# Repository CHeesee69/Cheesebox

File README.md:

# Cheesebox
The cheesebox is a small emulation device that uses a CM5 board. It will have the power to emulate 5th-gen and select 6th- and 7th-gen hardware. I plan for it to be kind of flat so I can make a screen, battery, and controller add-on down the line to make it portable. Why is it called "The Cheesebox"? Because I like cheese. Duh.

# Features

Cool Design

Power Light

Two USB-C Ports

Two USB-A 3.0 Ports

Two USB-A 2.0 Ports

Magjack Ethernet Port

3.5 mm Headphone Jack

Micro SD Card Slot

2242 M.2 SSD or NVMe Slot (3rd Gen)

HDMI Output

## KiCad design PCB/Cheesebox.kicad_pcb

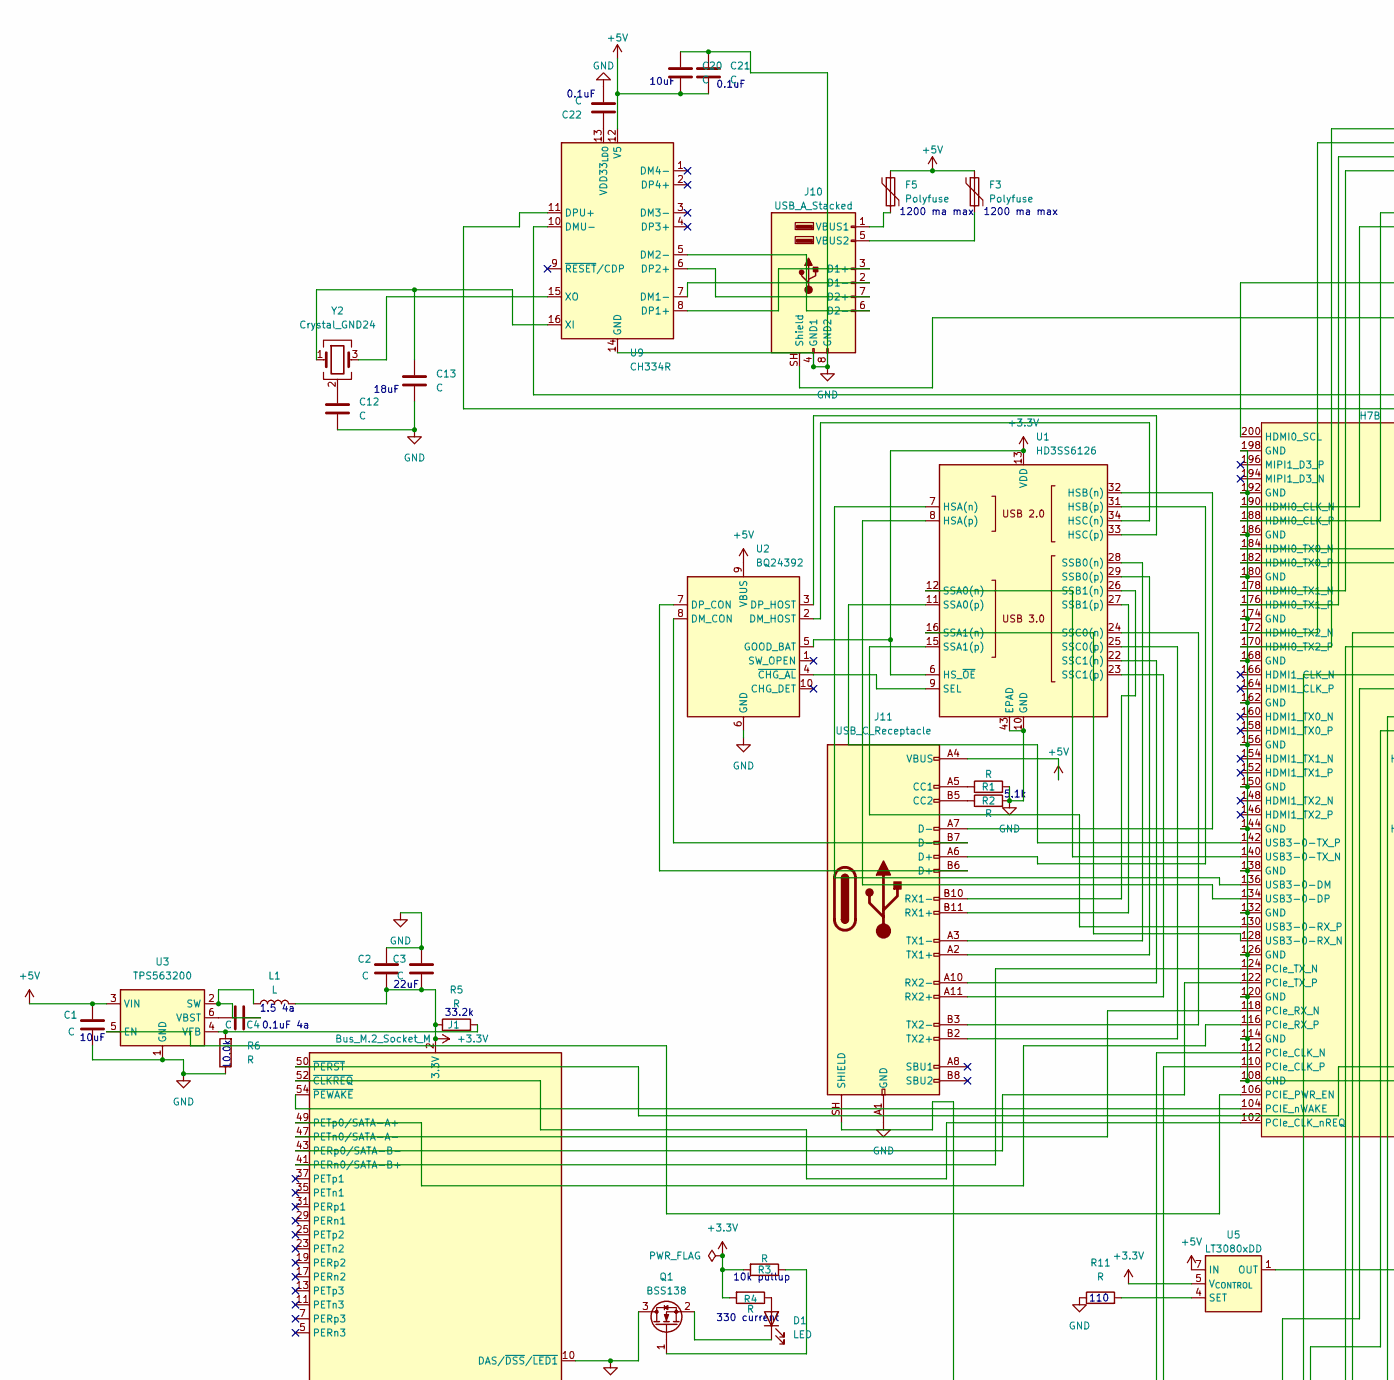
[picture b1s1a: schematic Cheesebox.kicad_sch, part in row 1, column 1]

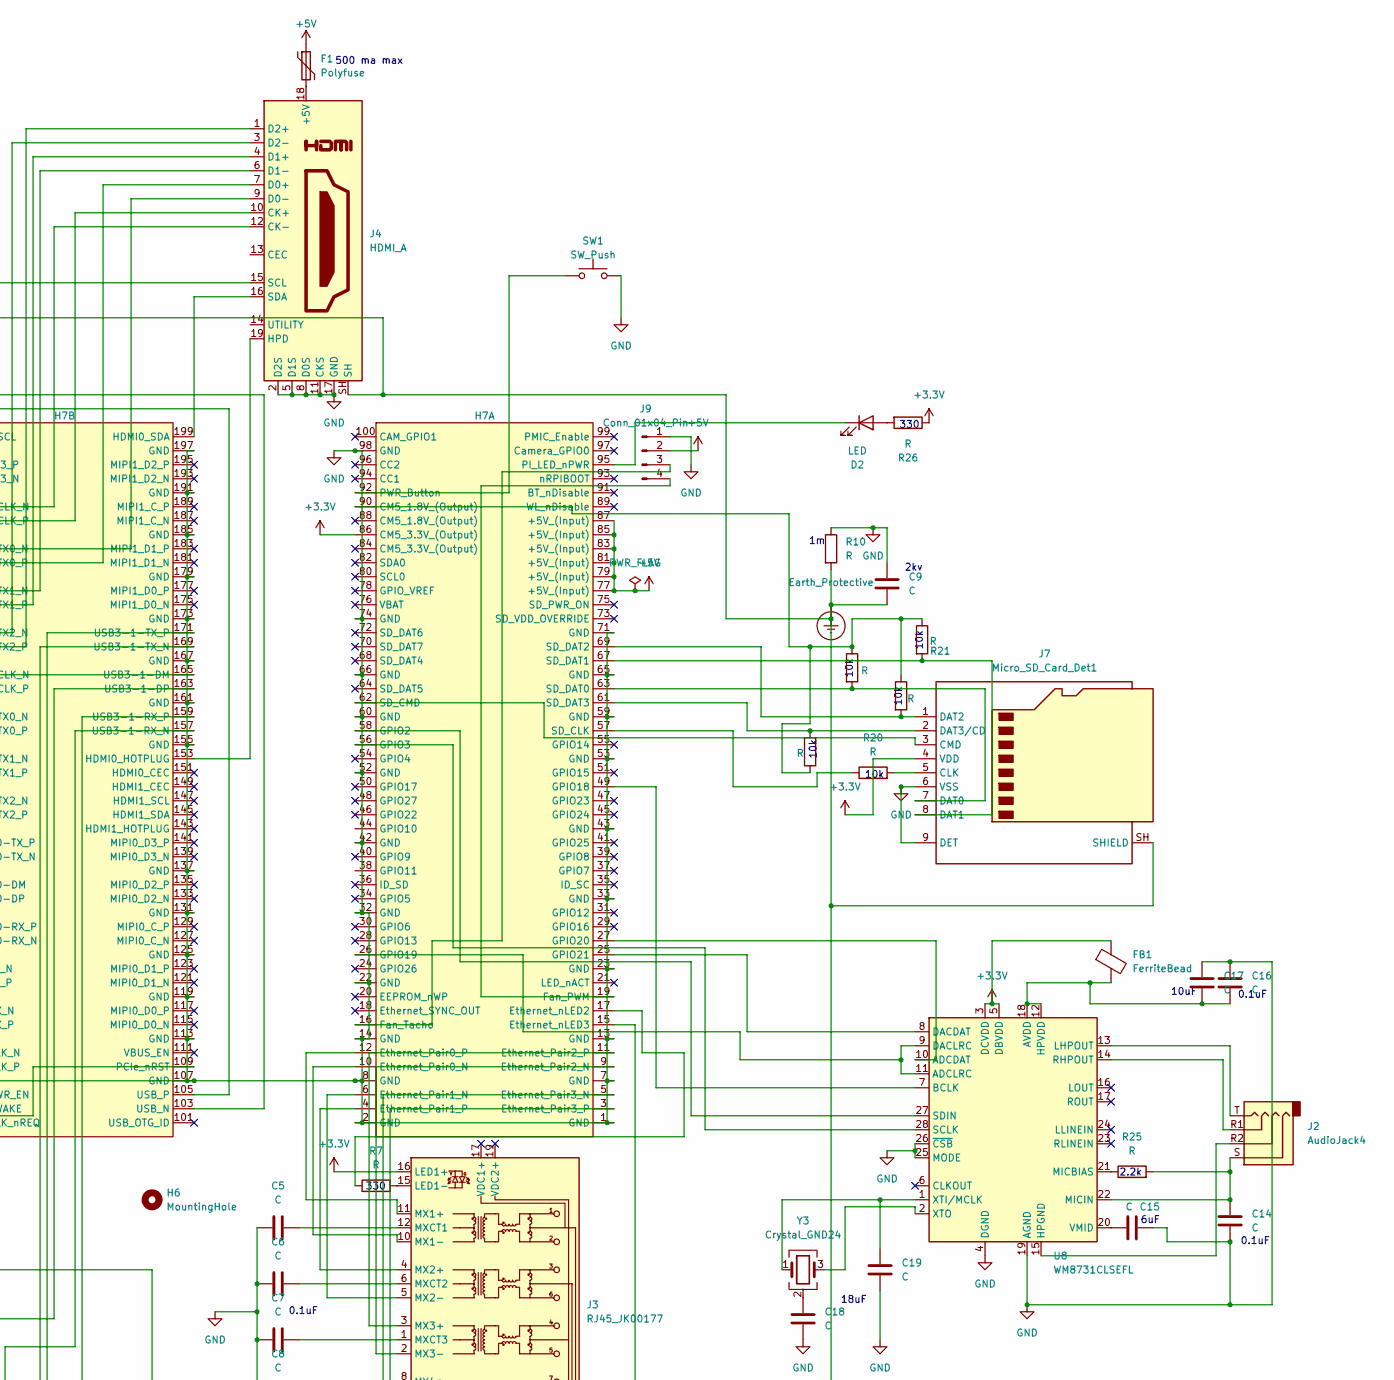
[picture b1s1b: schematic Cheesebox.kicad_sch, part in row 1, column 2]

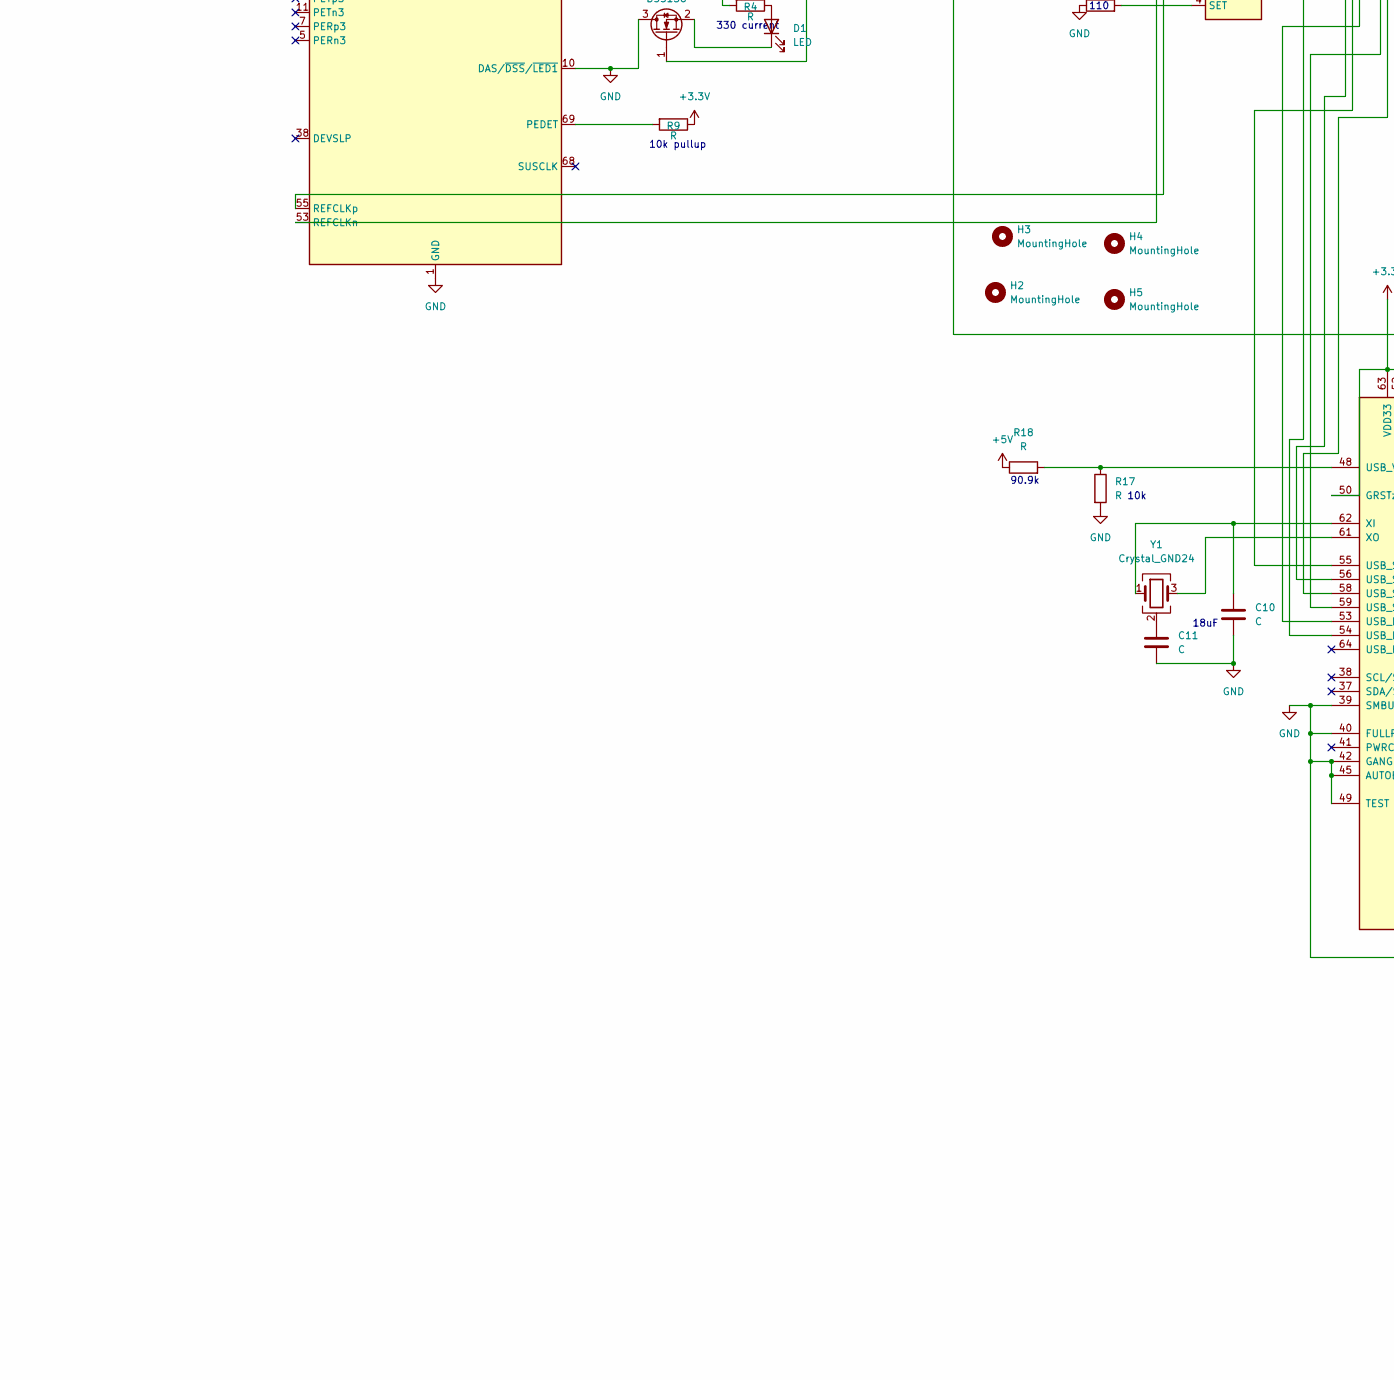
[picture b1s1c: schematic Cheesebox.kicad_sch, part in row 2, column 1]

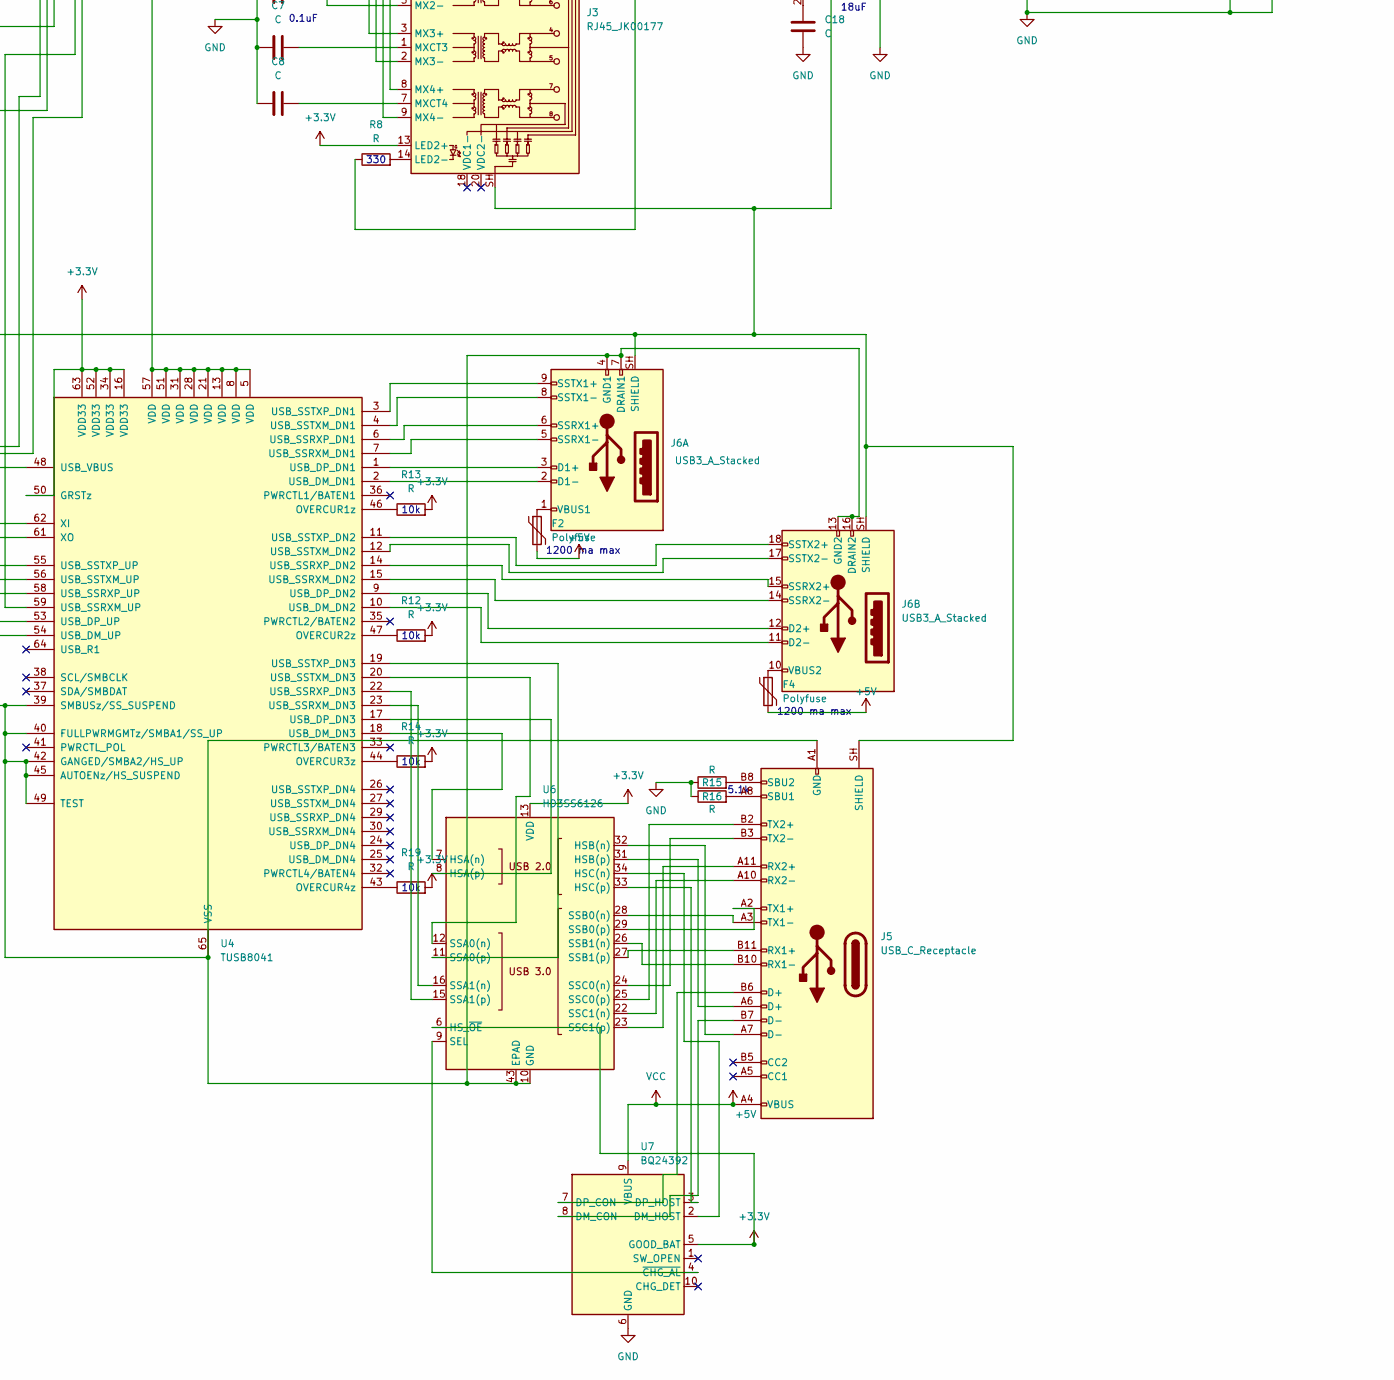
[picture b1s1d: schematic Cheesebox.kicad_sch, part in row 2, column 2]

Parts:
C1, C2, C3, C10, C11, C12, C13, C15, C17, C18, C19, C20: C; C_0805_2012Metric_Pad1.18x1.45mm_HandSolder
C4, C5, C6, C7, C8, C9, C14, C16, C21, C22: C; C_0603_1608Metric_Pad1.08x0.95mm_HandSolder
D1, D2: LED; LED_0603_1608Metric_Pad1.05x0.95mm_HandSolder
F1: Polyfuse; Fuse_1206_3216Metric_Pad1.42x1.75mm_HandSolder
F2, F3, F4, F5: Polyfuse; Fuse_1210_3225Metric_Pad1.42x2.65mm_HandSolder
FB1: FerriteBead; L_0805_2012Metric_Pad1.05x1.20mm_HandSolder
H2, H3, H4, H5: MountingHole; MountingHole_2.5mm
H6: MountingHole; MountingHole_2.2mm_M2
H7: RaspberryPi-CM5-Carrier-Short-NPTH-Silk
J1: Bus_M.2_Socket_M; CONN67_2199230_TEC
J2: AudioJack4; Jack_3.5mm_CUI_SJ-3524-SMT_Horizontal
J3: RJ45_JK00177; RJ45_Pulse_JK00177NL_Horizontal
J4: HDMI_A; HDMI_A_Amphenol_10029449-x01xLF_Horizontal
J5, J11: USB_C_Receptacle; USB_C_Receptacle_Amphenol_12401548E4-2A_CircularHoles
J6: USB3_A_Stacked; USB3_A_Molex_48406-0001_Horizontal_Stacked
J7: Micro_SD_Card_Det1; microSD_HC_Hirose_DM3AT-SF-PEJM5
J9: Conn_01x04_Pin; FanPinHeader_1x04_P2.54mm_Vertical
J10: USB_A_Stacked; USB_A_Wuerth_61400826021_Horizontal_Stacked
L1: L; L_Coilcraft_XAL4040-XXX
Q1: BSS138; SOT-23
R1, R2, R3, R4, R7, R8, R9, R10, R11, R12, R13, R14, R15, R16, R19, R20, R21, R22, R23, R24, R25, R26: R; R_0805_2012Metric_Pad1.20x1.40mm_HandSolder
R5, R6, R17, R18: R; R_1206_3216Metric_Pad1.30x1.75mm_HandSolder
SW1: SW_Push; SW_PUSH_6mm_H5mm
U1, U6: HD3SS6126; WQFN-42-1EP_3.5x9mm_P0.5mm_EP2.05x7.55mm_ThermalVias
U2, U7: BQ24392; Texas_R-PUQFN-N10
U3: TPS563200; SOT-23-6
U4: TUSB8041; QFN-64-1EP_9x9mm_P0.5mm_EP6x6mm_ThermalVias
U5: LT3080xDD; DFN-8-1EP_3x3mm_P0.5mm_EP1.66x2.38mm
U8: WM8731CLSEFL; QFN-28-1EP_5x5mm_P0.5mm_EP3.35x3.35mm
U9: CH334R; QSOP-16_3.9x4.9mm_P0.635mm
Y1, Y2, Y3: Crystal_GND24; Resonator-3Pin_W6.0mm_H3.0mm

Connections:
+3.3V: C2.2, C3.2, FB1.1, H7.86 (CM5_3.3V_(Output)), J1.2 (3.3V), J1.4 (3.3V), J1.12 (3.3V), J1.14 (3.3V), J1.16 (3.3V), J1.18 (3.3V), J1.70 (3.3V), J1.72 (3.3V), J1.74 (3.3V), J3.13 (LED2+), J3.16 (LED1+), J7.4 (VDD), L1.2, R3.2, R4.2, R5.1, R9.1, R12.2, R13.2, R14.2, R19.2, R26.1, U1.6 (HS_~OE), U1.13 (VDD), U1.20 (VDD), U1.30 (VDD), U2.5 (GOOD_BAT), U4.16 (VDD33), U4.34 (VDD33), U4.50 (GRSTz), U4.52 (VDD33), U4.63 (VDD33), U5.5 (V_{CONTROL}), U6.6 (HS_~OE), U6.13 (VDD), U6.20 (VDD), U6.30 (VDD), U7.5 (GOOD_BAT), U8.3 (DCVDD), U8.5 (DBVDD)
+5V: C1.1, C20.1, C21.2, F1.1, F2.2, F3.1, F4.2, F5.1, H7.77 (+5V_(Input)), H7.79 (+5V_(Input)), H7.81 (+5V_(Input)), H7.83 (+5V_(Input)), H7.85 (+5V_(Input)), H7.87 (+5V_(Input)), J5.A4 (VBUS), J5.A9 (VBUS), J5.B4 (VBUS), J5.B9 (VBUS), J9.2, J11.A4 (VBUS), J11.A9 (VBUS), J11.B4 (VBUS), J11.B9 (VBUS), R18.1, U2.9 (VBUS), U3.3 (VIN), U5.7 (IN), U5.8 (IN), U7.9 (VBUS), U9.12 (V5)
Earth_Protective: C9.2, J3.SH, J4.SH, J5.SH (SHIELD), J6.SH (SHIELD), J7.SH (SHIELD), J10.SH (Shield), J11.SH (SHIELD), R10.2
GND: C1.2, C2.1, C3.1, C5.1, C6.1, C7.1, C8.1, C9.1, C10.1, C11.1, C12.1, C13.1, C14.2, C15.1, C16.1, C17.2, C18.1, C19.1, C20.2, C21.1, C22.2, H7.1 (GND), H7.2 (GND), H7.7 (GND), H7.8 (GND), H7.13 (GND), H7.14 (GND), H7.22 (GND), H7.23 (GND), H7.32 (GND), H7.33 (GND), H7.42 (GND), H7.43 (GND), H7.52 (GND), H7.53 (GND), H7.59 (GND), H7.60 (GND), H7.65 (GND), H7.66 (GND), H7.71 (GND), H7.74 (GND), H7.98 (GND), H7.107 (GND), H7.108 (GND), H7.113 (GND), H7.114 (GND), H7.119 (GND), H7.120 (GND), H7.125 (GND), H7.126 (GND), H7.131 (GND), H7.132 (GND), H7.137 (GND), H7.138 (GND), H7.144 (GND), H7.150 (GND), H7.155 (GND), H7.156 (GND), H7.161 (GND), H7.162 (GND), H7.167 (GND), H7.168 (GND), H7.173 (GND), H7.174 (GND), H7.179 (GND), H7.180 (GND), H7.185 (GND), H7.186 (GND), H7.191 (GND), H7.192 (GND), H7.197 (GND), H7.198 (GND), J1.1 (GND), J1.3 (GND), J1.9 (GND), J1.10 (DAS/~DSS/~LED1), J1.15 (GND), J1.21 (GND), J1.27 (GND), J1.33 (GND), J1.39 (GND), J1.45 (GND), J1.51 (GND), J1.57 (GND), J1.71 (GND), J1.73 (GND), J1.75 (GND), J4.2 (D2S), J4.5 (D1S), J4.8 (D0S), J4.11 (CKS), J4.17 (GND), J5.A1 (GND), J5.A12 (GND), J5.B1 (GND), J5.B12 (GND), J6.4 (GND1), J6.7 (DRAIN1), J6.13 (GND2), J6.16 (DRAIN2), J7.6 (VSS), J7.9 (DET), J9.1, J10.4 (GND1), J10.8 (GND2), J11.A1 (GND), J11.A12 (GND), J11.B1 (GND), J11.B12 (GND), Q1.3 (D), R1.2, R2.2, R6.1, R10.1, R11.1, R15.1, R16.1, R17.2, SW1.2, U1.10 (GND), U1.14 (GND), U1.17 (GND), U1.19 (GND), U1.21 (GND), U1.43 (EPAD), U2.6 (GND), U3.1 (GND), U4.39 (SMBUSz/SS_SUSPEND), U4.40 (FULLPWRMGMTz/SMBA1/SS_UP), U4.42 (GANGED/SMBA2/HS_UP), U4.45 (AUTOENz/HS_SUSPEND), U4.49 (TEST), U4.65 (VSS), U6.10 (GND), U6.14 (GND), U6.17 (GND), U6.19 (GND), U6.21 (GND), U6.43 (EPAD), U7.6 (GND), U8.4 (DGND), U8.19 (AGND), U8.25 (MODE), U8.26 (~CSB), U8.29 (AGND), U9.14 (GND)
unnamed: C11.2, Y1.2 (G), Y1.4 (G)
unnamed: C12.2, Y2.2 (G), Y2.4 (G)
unnamed: C18.2, Y3.2 (G), Y3.4 (G)
unnamed: D1.2 (A), R4.1
unnamed: D1.1 (K), Q1.2 (S)
unnamed: D2.2 (A), R26.2
unnamed: D2.1 (K), H7.95 (PI_LED_nPWR)
unnamed: H7.90 (CM5_1.8V_(Output)), R21.1, R22.1, R23.1, R24.1
unnamed: H7.10 (Ethernet_Pair0_N), J3.10 (MX1-)
unnamed: H7.12 (Ethernet_Pair0_P), J3.11 (MX1+)
unnamed: H7.6 (Ethernet_Pair1_N), J3.5 (MX2-)
unnamed: H7.4 (Ethernet_Pair1_P), J3.4 (MX2+)
unnamed: H7.9 (Ethernet_Pair2_N), J3.2 (MX3-)
unnamed: H7.11 (Ethernet_Pair2_P), J3.3 (MX3+)
unnamed: H7.5 (Ethernet_Pair3_N), J3.9 (MX4-)
unnamed: H7.3 (Ethernet_Pair3_P), J3.8 (MX4+)
unnamed: H7.17 (Ethernet_nLED2), R7.1
unnamed: H7.15 (Ethernet_nLED3), R8.1
unnamed: H7.19 (Fan_PWM), J9.4
unnamed: H7.16 (Fan_Tacho), J9.3
unnamed: H7.58 (GPIO2), U8.27 (SDIN)
unnamed: H7.56 (GPIO3), U8.28 (SCLK)
unnamed: H7.49 (GPIO18), U8.7 (BCLK)
unnamed: H7.26 (GPIO19), U8.9 (DACLRC), U8.11 (ADCLRC)
unnamed: H7.27 (GPIO20), U8.10 (ADCDAT)
unnamed: H7.25 (GPIO21), U8.8 (DACDAT)
unnamed: H7.92 (PWR_Button), SW1.1
unnamed: H7.57 (SD_CLK), R20.1
unnamed: H7.62 (SD_CMD), J7.3 (CMD)
unnamed: H7.63 (SD_DAT0), J7.7 (DAT0), R22.2
unnamed: H7.67 (SD_DAT1), J7.8 (DAT1), R21.2
unnamed: H7.69 (SD_DAT2), J7.1 (DAT2), R23.2
unnamed: H7.61 (SD_DAT3), J7.2 (DAT3/CD), R24.2
unnamed: H7.190 (HDMI0_CLK_N), J4.12 (CK-)
unnamed: H7.188 (HDMI0_CLK_P), J4.10 (CK+)
unnamed: H7.153 (HDMI0_HOTPLUG), J4.19 (HPD)
unnamed: H7.200 (HDMI0_SCL), J4.15 (SCL)
unnamed: H7.199 (HDMI0_SDA), J4.16 (SDA)
unnamed: H7.184 (HDMI0_TX0_N), J4.9 (D0-)
unnamed: H7.182 (HDMI0_TX0_P), J4.7 (D0+)
unnamed: H7.178 (HDMI0_TX1_N), J4.6 (D1-)
unnamed: H7.176 (HDMI0_TX1_P), J4.4 (D1+)
unnamed: H7.172 (HDMI0_TX2_N), J4.3 (D2-)
unnamed: H7.170 (HDMI0_TX2_P), J4.1 (D2+)
unnamed: H7.106 (PCIE_PWR_EN), U3.5 (EN)
unnamed: H7.104 (PCIE_nWAKE), J1.54 (~PEWAKE)
unnamed: H7.112 (PCIe_CLK_N), J1.53 (REFCLKn)
unnamed: H7.110 (PCIe_CLK_P), J1.55 (REFCLKp)
unnamed: H7.102 (PCIe_CLK_nREQ), J1.52 (~CLKREQ)
unnamed: H7.118 (PCIe_RX_N), J1.47 (PETn0/SATA-A-)
unnamed: H7.116 (PCIe_RX_P), J1.49 (PETp0/SATA-A+)
unnamed: H7.124 (PCIe_TX_N), J1.41 (PERn0/SATA-B+)
unnamed: H7.122 (PCIe_TX_P), J1.43 (PERp0/SATA-B-)
unnamed: H7.109 (PCIe_nRST), J1.50 (~PERST)
unnamed: H7.136 (USB3-0-DM), U1.7 (HSA(n))
unnamed: H7.134 (USB3-0-DP), U1.8 (HSA(p))
unnamed: H7.128 (USB3-0-RX_N), U1.16 (SSA1(n))
unnamed: H7.130 (USB3-0-RX_P), U1.15 (SSA1(p))
unnamed: H7.140 (USB3-0-TX_N), U1.12 (SSA0(n))
unnamed: H7.142 (USB3-0-TX_P), U1.11 (SSA0(p))
unnamed: H7.165 (USB3-1-DM), U4.54 (USB_DM_UP)
unnamed: H7.163 (USB3-1-DP), U4.53 (USB_DP_UP)
unnamed: H7.157 (USB3-1-RX_N), U4.59 (USB_SSRXM_UP)
unnamed: H7.159 (USB3-1-RX_P), U4.58 (USB_SSRXP_UP)
unnamed: H7.169 (USB3-1-TX_N), U4.56 (USB_SSTXM_UP)
unnamed: H7.171 (USB3-1-TX_P), U4.55 (USB_SSTXP_UP)
unnamed: H7.103 (USB_N), U9.10 (DMU-)
unnamed: H7.105 (USB_P), U9.11 (DPU+)
unnamed: J1.69 (PEDET), R9.2
unnamed: J3.15 (LED1-), R7.2
unnamed: J3.14 (LED2-), R8.2
unnamed: C5.2, J3.12 (MXCT1)
unnamed: C6.2, J3.6 (MXCT2)
unnamed: C7.2, J3.1 (MXCT3)
unnamed: C8.2, J3.7 (MXCT4)
unnamed: F1.2, J4.18 (+5V)
unnamed: J5.B11 (RX1+), U6.27 (SSB1(p))
unnamed: J5.B10 (RX1-), U6.26 (SSB1(n))
unnamed: J5.A11 (RX2+), U6.23 (SSC1(p))
unnamed: J5.A10 (RX2-), U6.22 (SSC1(n))
unnamed: J5.A8 (SBU1), R16.2
unnamed: J5.B8 (SBU2), R15.2
unnamed: J5.A2 (TX1+), U6.29 (SSB0(p))
unnamed: J5.A3 (TX1-), U6.28 (SSB0(n))
unnamed: J5.B2 (TX2+), U6.25 (SSC0(p))
unnamed: J5.B3 (TX2-), U6.24 (SSC0(n))
unnamed: J6.3 (D1+), U4.1 (USB_DP_DN1)
unnamed: J6.2 (D1-), U4.2 (USB_DM_DN1)
unnamed: J6.6 (SSRX1+), U4.6 (USB_SSRXP_DN1)
unnamed: J6.5 (SSRX1-), U4.7 (USB_SSRXM_DN1)
unnamed: J6.9 (SSTX1+), U4.3 (USB_SSTXP_DN1)
unnamed: J6.8 (SSTX1-), U4.4 (USB_SSTXM_DN1)
unnamed: F2.1, J6.1 (VBUS1)
unnamed: J6.12 (D2+), U4.9 (USB_DP_DN2)
unnamed: J6.11 (D2-), U4.10 (USB_DM_DN2)
unnamed: J6.15 (SSRX2+), U4.14 (USB_SSRXP_DN2)
unnamed: J6.14 (SSRX2-), U4.15 (USB_SSRXM_DN2)
unnamed: J6.18 (SSTX2+), U4.11 (USB_SSTXP_DN2)
unnamed: J6.17 (SSTX2-), U4.12 (USB_SSTXM_DN2)
unnamed: F4.1, J6.10 (VBUS2)
unnamed: J7.5 (CLK), R20.2
unnamed: J10.3 (D1+), U9.8 (DP1+)
unnamed: J10.2 (D1-), U9.7 (DM1-)
unnamed: J10.7 (D2+), U9.6 (DP2+)
unnamed: J10.6 (D2-), U9.5 (DM2-)
unnamed: F5.2, J10.1 (VBUS1)
unnamed: F3.2, J10.5 (VBUS2)
unnamed: J11.A5 (CC1), R1.1
unnamed: J11.B5 (CC2), R2.1
unnamed: J11.B11 (RX1+), U1.27 (SSB1(p))
unnamed: J11.B10 (RX1-), U1.26 (SSB1(n))
unnamed: J11.A11 (RX2+), U1.23 (SSC1(p))
unnamed: J11.A10 (RX2-), U1.22 (SSC1(n))
unnamed: J11.A2 (TX1+), U1.29 (SSB0(p))
unnamed: J11.A3 (TX1-), U1.28 (SSB0(n))
unnamed: J11.B2 (TX2+), U1.25 (SSC0(p))
unnamed: J11.B3 (TX2-), U1.24 (SSC0(n))
unnamed: Q1.1 (G), R3.1
unnamed: J11.A7 (D-), U1.32 (HSB(n))
unnamed: J11.A6 (D+), U1.31 (HSB(p))
unnamed: U1.34 (HSC(n)), U2.2 (DM_HOST)
unnamed: U1.33 (HSC(p)), U2.3 (DP_HOST)
unnamed: U1.9 (SEL), U2.4 (~CHG_AL)
unnamed: J11.B7 (D-), U2.8 (DM_CON)
unnamed: J11.B6 (D+), U2.7 (DP_CON)
unnamed: C4.2, L1.1, U3.2 (SW)
unnamed: C4.1, U3.6 (VBST)
unnamed: R5.2, R6.2, U3.4 (VFB)
unnamed: R13.1, U4.46 (OVERCUR1z)
unnamed: R12.1, U4.47 (OVERCUR2z)
unnamed: R14.1, U4.44 (OVERCUR3z)
unnamed: R19.1, U4.43 (OVERCUR4z)
unnamed: U4.18 (USB_DM_DN3), U6.7 (HSA(n))
unnamed: U4.17 (USB_DP_DN3), U6.8 (HSA(p))
unnamed: U4.23 (USB_SSRXM_DN3), U6.16 (SSA1(n))
unnamed: U4.22 (USB_SSRXP_DN3), U6.15 (SSA1(p))
unnamed: U4.20 (USB_SSTXM_DN3), U6.12 (SSA0(n))
unnamed: U4.19 (USB_SSTXP_DN3), U6.11 (SSA0(p))
unnamed: R17.1, R18.2, U4.48 (USB_VBUS)
unnamed: U4.5 (VDD), U4.8 (VDD), U4.13 (VDD), U4.21 (VDD), U4.28 (VDD), U4.31 (VDD), U4.51 (VDD), U4.57 (VDD), U5.1 (OUT), U5.2 (OUT), U5.3 (OUT), U5.9 (OUT)
unnamed: C10.2, U4.62 (XI), Y1.1
unnamed: U4.61 (XO), Y1.3
unnamed: R11.2, U5.4 (SET)
unnamed: J5.A7 (D-), U6.32 (HSB(n))
unnamed: J5.A6 (D+), U6.31 (HSB(p))
unnamed: U6.34 (HSC(n)), U7.2 (DM_HOST)
unnamed: U6.33 (HSC(p)), U7.3 (DP_HOST)
unnamed: U6.9 (SEL), U7.4 (~CHG_AL)
unnamed: J5.B7 (D-), U7.8 (DM_CON)
unnamed: J5.B6 (D+), U7.7 (DP_CON)
unnamed: C16.2, C17.1, FB1.2, U8.12 (HPVDD), U8.18 (AVDD)
unnamed: J2.R2, U8.15 (HPGND)
unnamed: J2.T, U8.13 (LHPOUT)
unnamed: R25.1, U8.21 (MICBIAS)
unnamed: C14.1, J2.S, R25.2, U8.22 (MICIN)
unnamed: J2.R1, U8.14 (RHPOUT)
unnamed: C15.2, U8.20 (VMID)
unnamed: C19.2, U8.1 (XTI/MCLK), Y3.1
unnamed: U8.2 (XTO), Y3.3
unnamed: C22.1, U9.13 (VDD33_{LDO})
unnamed: C13.2, U9.16 (XI), Y2.1
unnamed: U9.15 (XO), Y2.3

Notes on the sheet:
10k
2kv
10uF
22uF
330
10k
1200 ma max
18uF
5.1k
33.2k
90.9k
10.0k
0.1uF
1.5 4a
330 current
110
10k pullup
6uF
0.1uF 4a
2.2k
500 ma max

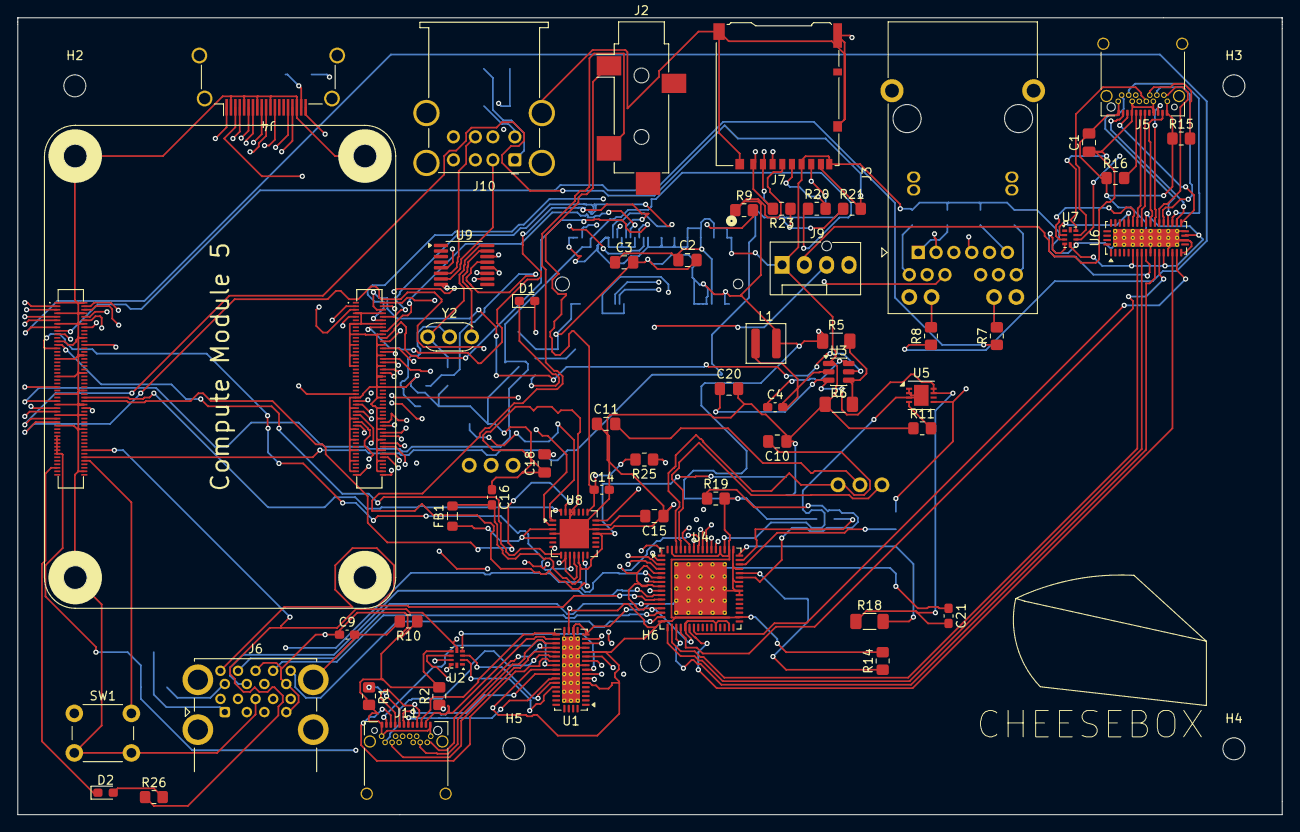
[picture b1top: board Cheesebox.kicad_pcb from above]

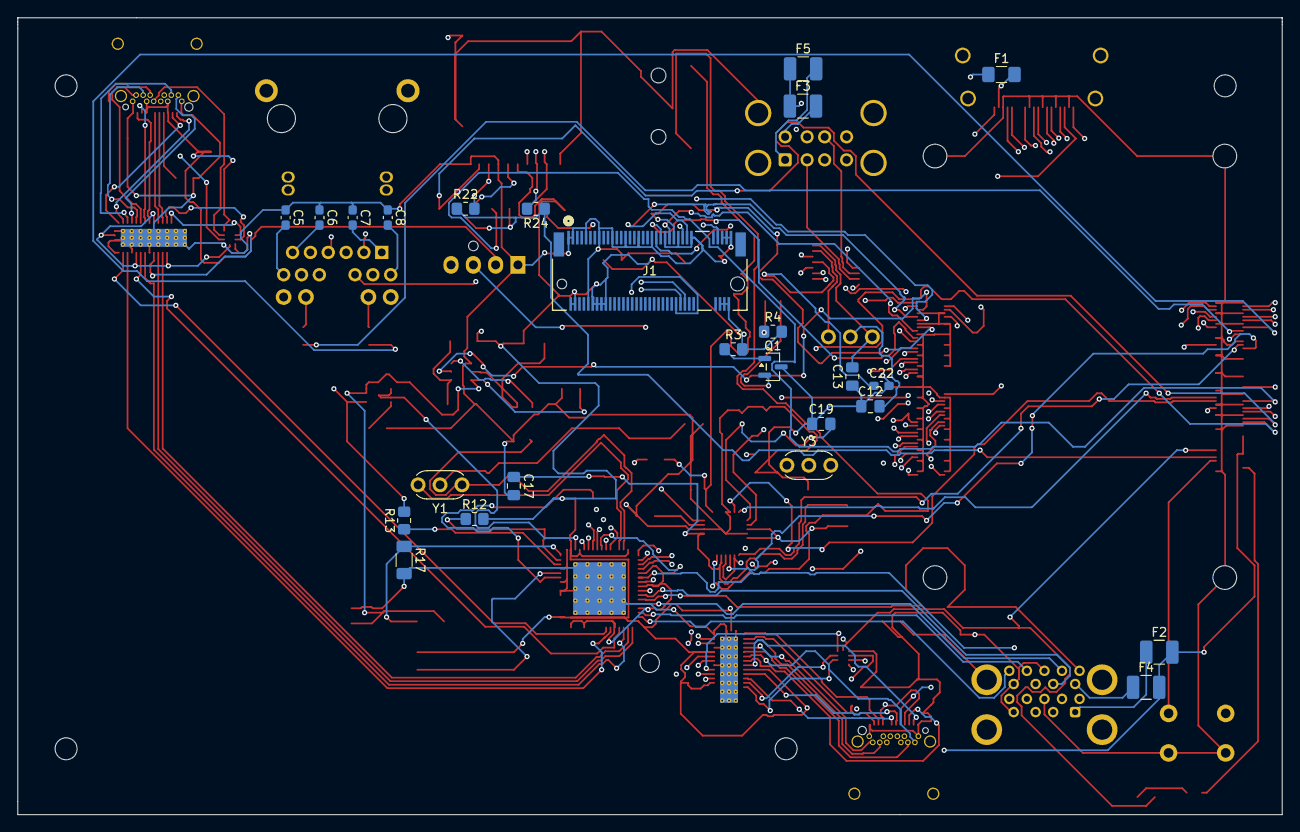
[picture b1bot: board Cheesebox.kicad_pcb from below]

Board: 6 copper layers, 144.0 x 90.8 mm, 87 parts (25 on the bottom side), 164 nets.

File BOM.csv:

"Id";"Designator";"Footprint";"Quantity";"Designation";"Supplier and ref";
1;"C1, C2, C3, C10, C11, C12, C13, C15, C17, C18, C19, C20";"C_0805_2012Metric_Pad1.18x1.45mm_HandSolder";12;"C";;;
2;"C4, C5, C6, C7, C8, C9, C14, C16, C21, C22";"C_0603_1608Metric_Pad1.08x0.95mm_HandSolder";10;"C";;;
3;"D1, D2";"LED_0603_1608Metric_Pad1.05x0.95mm_HandSolder";2;"LED";;;
4;"F1";"Fuse_1206_3216Metric_Pad1.42x1.75mm_HandSolder";1;"Polyfuse";;;
5;"F2, F3, F4, F5";"Fuse_1210_3225Metric_Pad1.42x2.65mm_HandSolder";4;"Polyfuse";;;
6;"FB1";"L_0805_2012Metric_Pad1.05x1.20mm_HandSolder";1;"FerriteBead";;;
7;"H7";"RaspberryPi-CM5-Carrier-Short-NPTH-Silk";1;"~";;;
8;"J1";"CONN67_2199230_TEC";1;"Bus_M.2_Socket_M";;;
9;"J2";"Jack_3.5mm_CUI_SJ-3524-SMT_Horizontal";1;"AudioJack4";;;
10;"J3";"RJ45_Pulse_JK00177NL_Horizontal";1;"RJ45_JK00177";;;
11;"J4";"HDMI_A_Amphenol_10029449-x01xLF_Horizontal";1;"HDMI_A";;;
12;"J5, J11";"USB_C_Receptacle_Amphenol_12401548E4-2A_CircularHoles";2;"USB_C_Receptacle";;;
13;"J6";"USB3_A_Molex_48406-0001_Horizontal_Stacked";1;"USB3_A_Stacked";;;
14;"J7";"microSD_HC_Hirose_DM3AT-SF-PEJM5";1;"Micro_SD_Card_Det1";;;
15;"J9";"FanPinHeader_1x04_P2.54mm_Vertical";1;"Conn_01x04_Pin";;;
16;"J10";"USB_A_Wuerth_61400826021_Horizontal_Stacked";1;"USB_A_Stacked";;;
17;"L1";"L_Coilcraft_XAL4040-XXX";1;"L";;;
18;"Q1";"SOT-23";1;"BSS138";;;
19;"R1, R2, R3, R4, R7, R8, R9, R10, R11, R12, R13, R14, R15, R16, R19, R20, R21, R22, R23, R24, R25, R26";"R_0805_2012Metric_Pad1.20x1.40mm_HandSolder";22;"R";;;
20;"R5, R6, R17, R18";"R_1206_3216Metric_Pad1.30x1.75mm_HandSolder";4;"R";;;
21;"SW1";"SW_PUSH_6mm_H5mm";1;"SW_Push";;;
22;"U1, U6";"WQFN-42-1EP_3.5x9mm_P0.5mm_EP2.05x7.55mm_ThermalVias";2;"HD3SS6126";;;
23;"U2, U7";"Texas_R-PUQFN-N10";2;"BQ24392";;;
24;"U3";"SOT-23-6";1;"TPS563200";;;
25;"U4";"QFN-64-1EP_9x9mm_P0.5mm_EP6x6mm_ThermalVias";1;"TUSB8041";;;
26;"U5";"DFN-8-1EP_3x3mm_P0.5mm_EP1.66x2.38mm";1;"LT3080xDD";;;
27;"U8";"QFN-28-1EP_5x5mm_P0.5mm_EP3.35x3.35mm";1;"WM8731CLSEFL";;;
28;"U9";"QSOP-16_3.9x4.9mm_P0.635mm";1;"CH334R";;;
29;"Y1, Y2, Y3";"Resonator-3Pin_W6.0mm_H3.0mm";3;"Crystal_GND24";;;
